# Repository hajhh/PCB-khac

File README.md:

# PCB-khac
CHE1082
CHE1086 2
CHE1092
CHE1058 5
CHE3045
CHE2008 2

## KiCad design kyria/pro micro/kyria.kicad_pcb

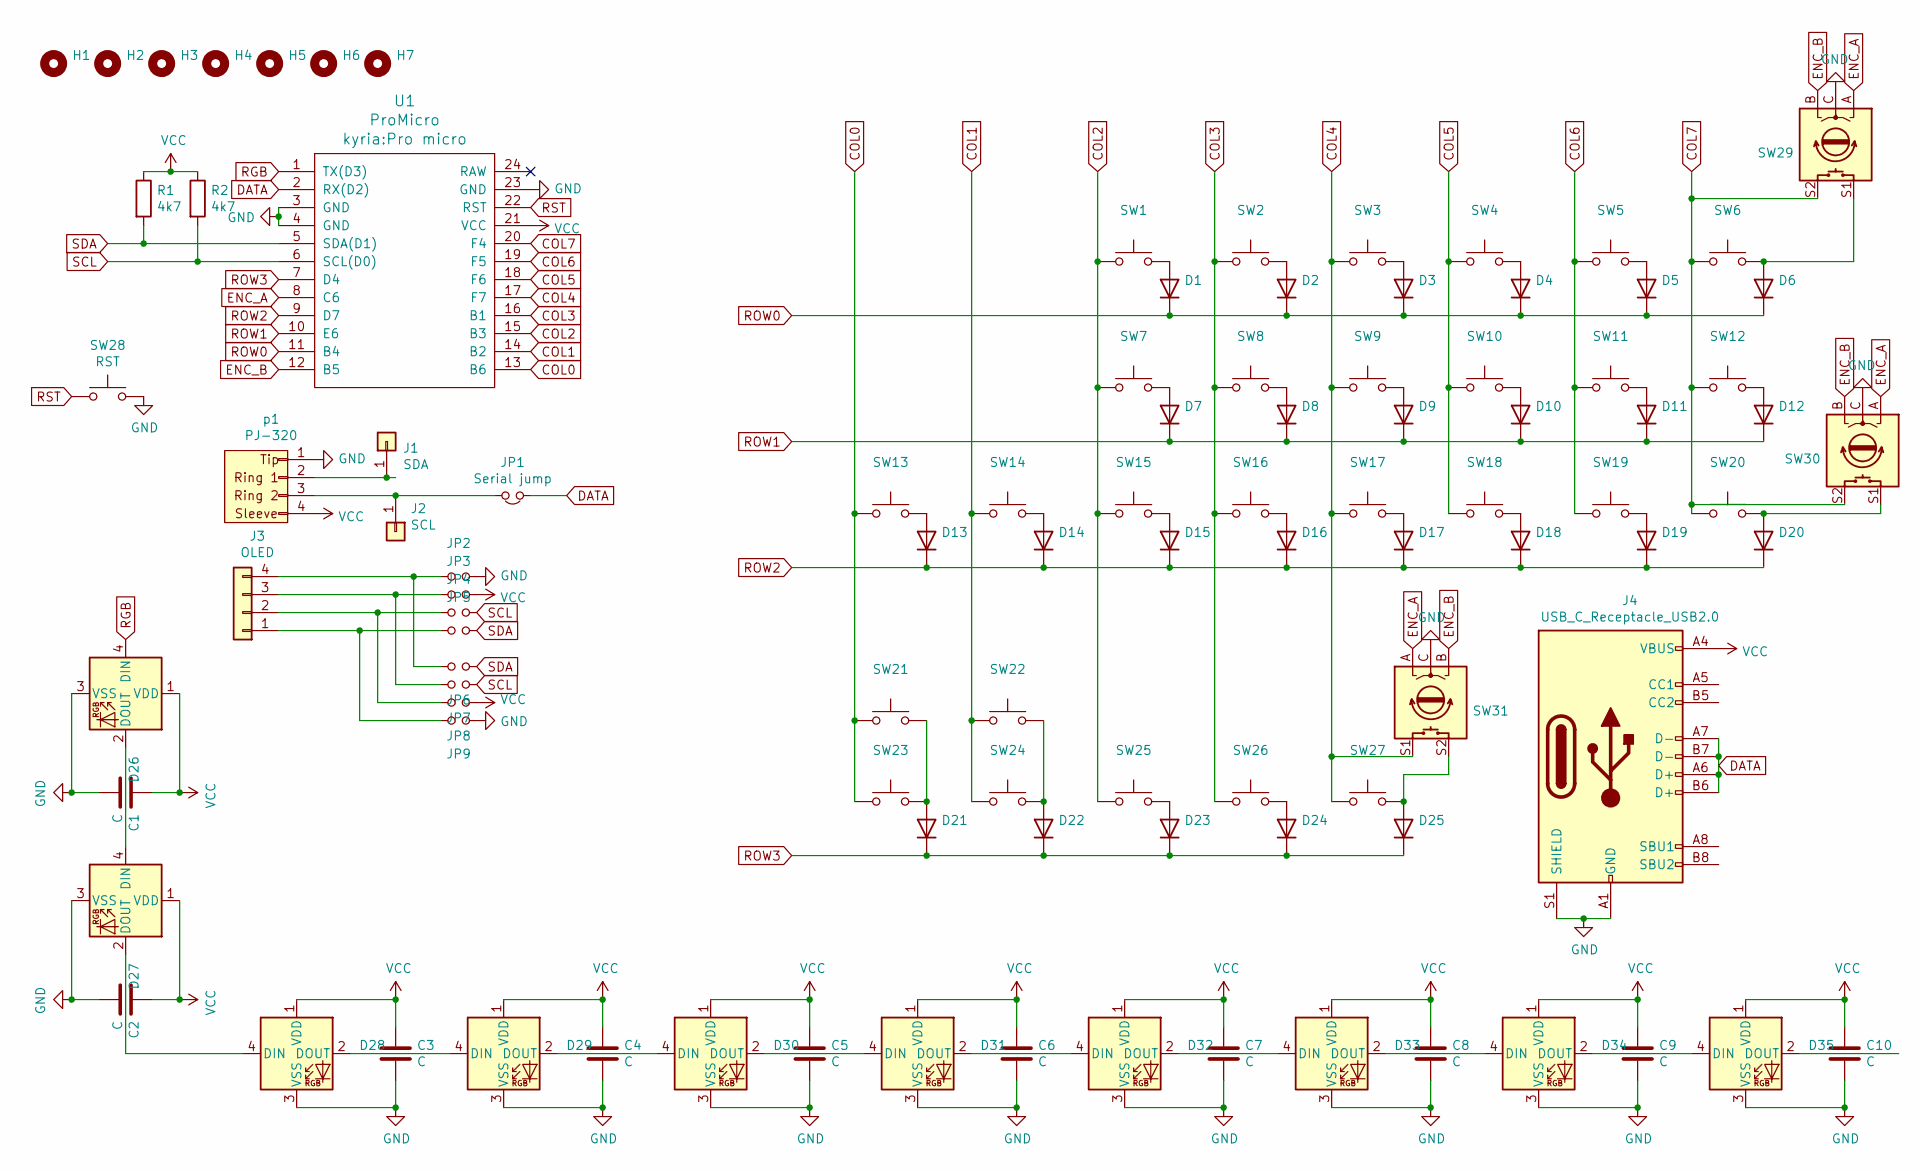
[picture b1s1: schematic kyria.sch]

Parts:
C1, C2, C3, C4, C5, C6, C7, C8, C9, C10: C
D1, D2, D3, D4, D5, D6, D7, D8, D9, D10, D11, D12, D13, D14, D15, D16, D17, D18, D19, D20, D21, D22, D23, D24, D25: Diode_2
D26, D27, D28, D29, D30, D31, D32, D33, D34, D35: WS2812B
H1, H2, H3, H4, H5, H6, H7: Hole
J1: SDA; testpoind
J2: SCL; testpoind
J3: OLED; Conn_01x04
J4: USB_C_Receptacle_USB2.0; TYPE C
JP1: Serial jump; JUMP_NO
JP2, JP3, JP4, JP5, JP6, JP7, JP8, JP9: JUMP_NO
R1, R2: 4k7; R_1
SW1, SW2, SW3, SW4, SW5, SW6, SW7, SW8, SW9, SW10, SW11, SW12, SW13, SW14, SW15, SW16, SW17, SW18, SW19, SW20, SW23, SW24, SW25, SW26, SW27: 1u
SW21, SW22: 2u
SW28: RST; SW_Tactile_SPST_Angled_PTS645Vx31-2LFS
SW29, SW30, SW31: ECODER
U1: ProMicro; Pro micro
p1: PJ-320; PJ-320A

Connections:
COL0: SW13.1, SW21.1, SW23.1, U1.13 (B6)
COL1: SW14.1, SW22.1, SW24.1, U1.14 (B2)
COL2: SW1.1, SW7.1, SW15.1, SW25.1, U1.15 (B3)
COL3: SW2.1, SW8.1, SW16.1, SW26.1, U1.16 (B1)
COL4: SW3.1, SW9.1, SW17.1, SW27.1, SW31.S1, U1.17 (F7)
COL5: SW4.1, SW10.1, SW18.1, U1.18 (F6)
COL6: SW5.1, SW11.1, SW19.1, U1.19 (F5)
COL7: SW6.2, SW12.2, SW20.2, SW29.S2, SW30.S2, U1.20 (F4)
DATA: J4.A6 (D+), J4.A7 (D-), J4.B6 (D+), J4.B7 (D-), JP1.1, U1.2 (RX(D2))
ENC_A: SW29.A, SW30.A, SW31.A, U1.8 (C6)
ENC_B: SW29.B, SW30.B, SW31.B, U1.12 (B5)
GND: C1.2, C2.2, C3.2, C4.2, C5.2, C6.2, C7.2, C8.2, C9.2, C10.2, D26.3 (VSS), D27.3 (VSS), D28.3 (VSS), D29.3 (VSS), D30.3 (VSS), D31.3 (VSS), D32.3 (VSS), D33.3 (VSS), D34.3 (VSS), D35.3 (VSS), J4.A1 (GND), J4.A12 (GND), J4.B1 (GND), J4.B12 (GND), J4.S1 (SHIELD), JP2.2, JP9.2, SW28.2, SW29.C, SW30.C, SW31.C, U1.3 (GND), U1.4 (GND), U1.23 (GND), p1.1
unnamed: D1.2 (A), SW1.2
unnamed: D2.2 (A), SW2.2
unnamed: D3.2 (A), SW3.2
unnamed: D4.2 (A), SW4.2
unnamed: D5.2 (A), SW5.2
unnamed: D6.2 (A), SW6.1, SW29.S1
unnamed: D7.2 (A), SW7.2
unnamed: D8.2 (A), SW8.2
unnamed: D9.2 (A), SW9.2
unnamed: D10.2 (A), SW10.2
unnamed: D11.2 (A), SW11.2
unnamed: D12.2 (A), SW12.1
unnamed: D13.2 (A), SW13.2
unnamed: D14.2 (A), SW14.2
unnamed: D15.2 (A), SW15.2
unnamed: D16.2 (A), SW16.2
unnamed: D17.2 (A), SW17.2
unnamed: D18.2 (A), SW18.2
unnamed: D19.2 (A), SW19.2
unnamed: D20.2 (A), SW20.1, SW30.S1
unnamed: D21.2 (A), SW21.2, SW23.2
unnamed: D22.2 (A), SW22.2, SW24.2
unnamed: D23.2 (A), SW25.2
unnamed: D24.2 (A), SW26.2
unnamed: D25.2 (A), SW27.2, SW31.S2
unnamed: D26.2 (DOUT), D27.4 (DIN)
unnamed: D27.2 (DOUT), D28.4 (DIN)
unnamed: D28.2 (DOUT), D29.4 (DIN)
unnamed: D29.2 (DOUT), D30.4 (DIN)
unnamed: D30.2 (DOUT), D31.4 (DIN)
unnamed: D31.2 (DOUT), D32.4 (DIN)
unnamed: D32.2 (DOUT), D33.4 (DIN)
unnamed: D33.2 (DOUT), D34.4 (DIN)
unnamed: D34.2 (DOUT), D35.4 (DIN)
unnamed: J1.1, p1.2
unnamed: J2.1, JP1.2, p1.3
unnamed: J3.1, JP5.1, JP9.1
unnamed: J3.2, JP4.1, JP8.1
unnamed: J3.3, JP3.1, JP7.1
unnamed: J3.4, JP2.1, JP6.1
RGB: D26.4 (DIN), U1.1 (TX(D3))
ROW0: D1.1 (K), D2.1 (K), D3.1 (K), D4.1 (K), D5.1 (K), D6.1 (K), U1.11 (B4)
ROW1: D7.1 (K), D8.1 (K), D9.1 (K), D10.1 (K), D11.1 (K), D12.1 (K), U1.10 (E6)
ROW2: D13.1 (K), D14.1 (K), D15.1 (K), D16.1 (K), D17.1 (K), D18.1 (K), D19.1 (K), D20.1 (K), U1.9 (D7)
ROW3: D21.1 (K), D22.1 (K), D23.1 (K), D24.1 (K), D25.1 (K), U1.7 (D4)
RST: SW28.1, U1.22 (RST)
SCL: JP4.2, JP7.2, R2.2, U1.6 (SCL(D0))
SDA: JP5.2, JP6.2, R1.2, U1.5 (SDA(D1))
VCC: C1.1, C2.1, C3.1, C4.1, C5.1, C6.1, C7.1, C8.1, C9.1, C10.1, D26.1 (VDD), D27.1 (VDD), D28.1 (VDD), D29.1 (VDD), D30.1 (VDD), D31.1 (VDD), D32.1 (VDD), D33.1 (VDD), D34.1 (VDD), D35.1 (VDD), J4.A4 (VBUS), J4.A9 (VBUS), J4.B4 (VBUS), J4.B9 (VBUS), JP3.2, JP8.2, R1.1, R2.1, U1.21 (VCC), p1.4

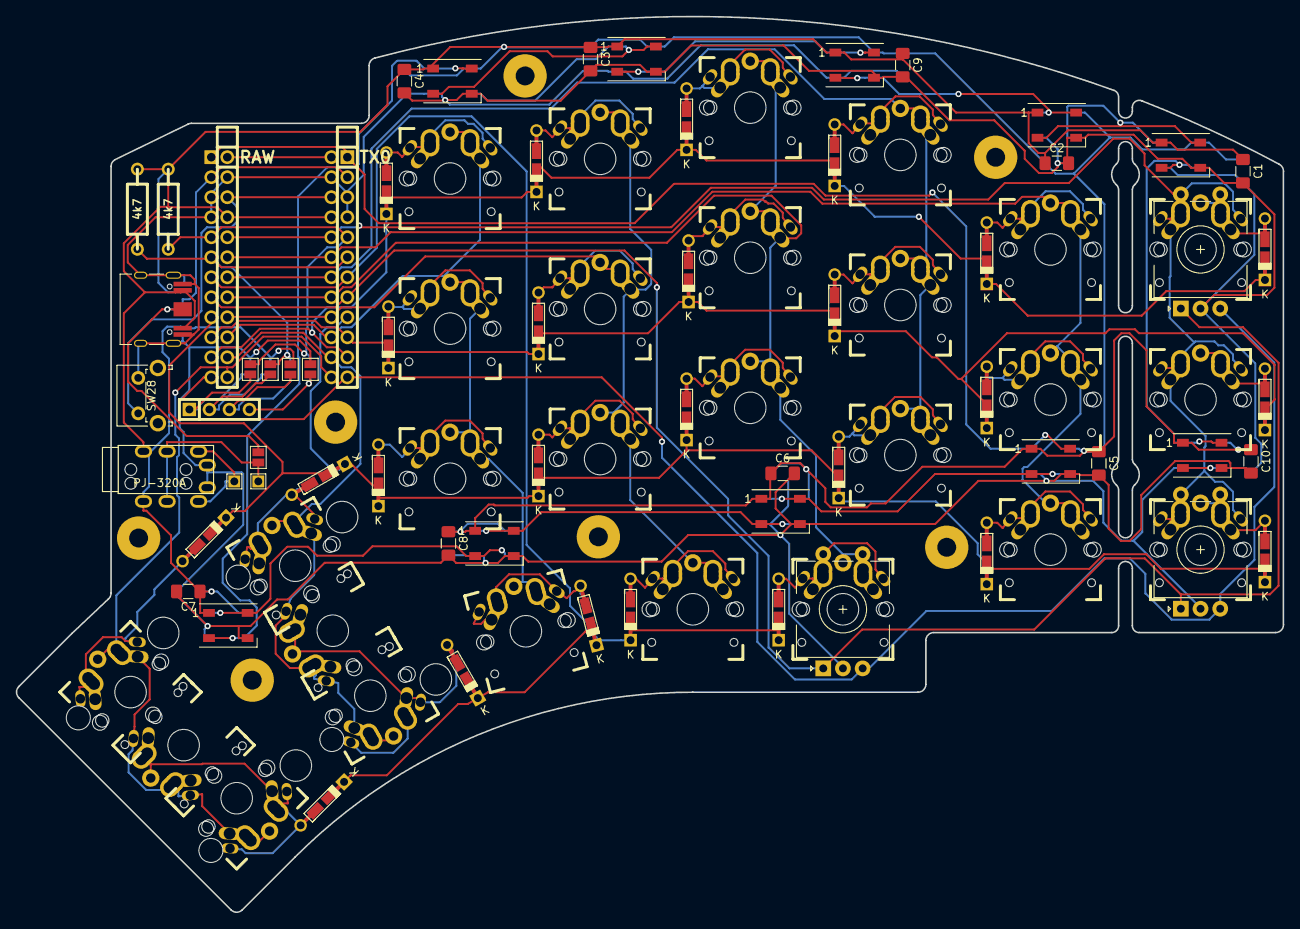
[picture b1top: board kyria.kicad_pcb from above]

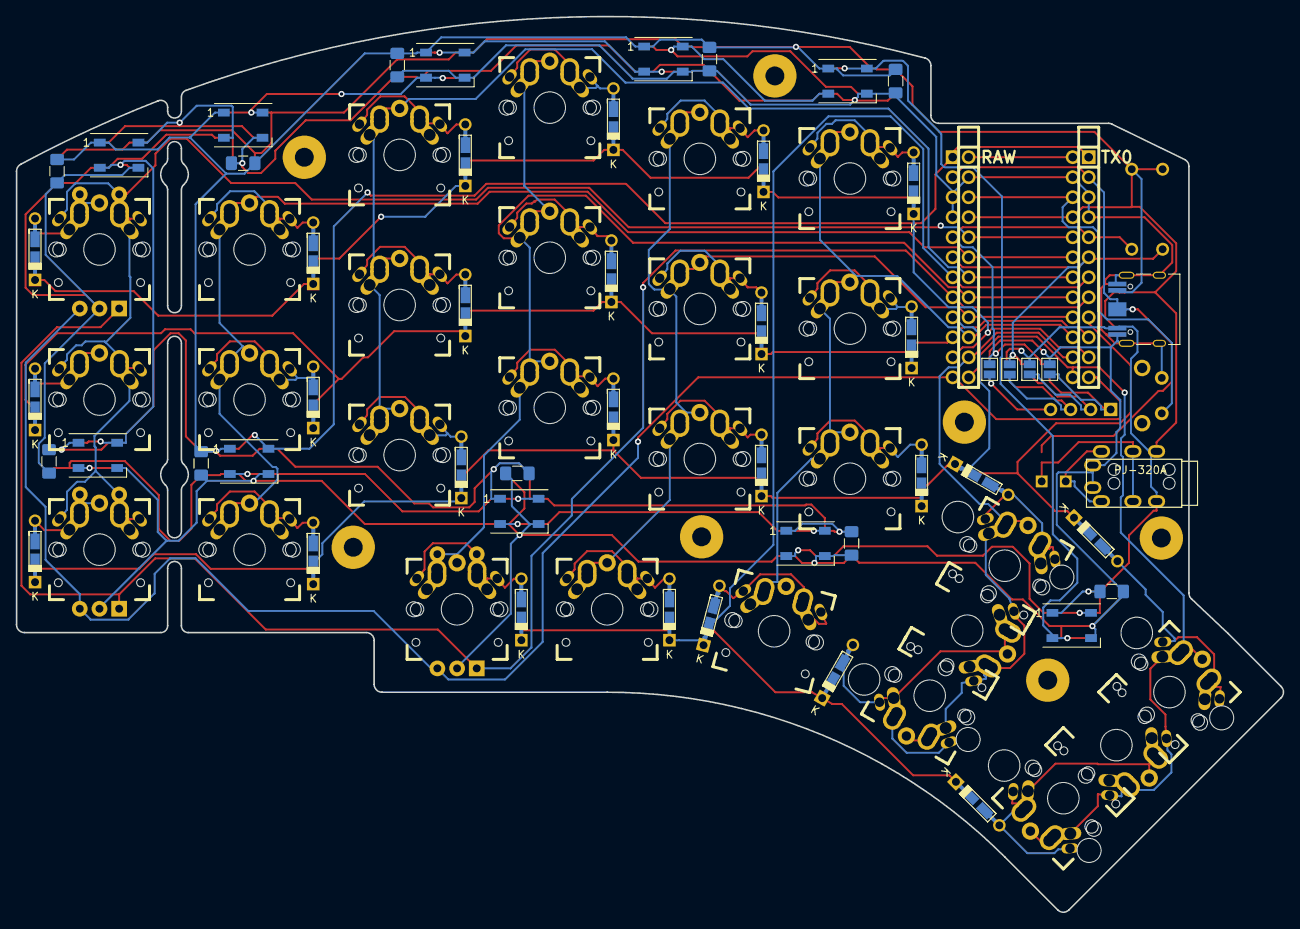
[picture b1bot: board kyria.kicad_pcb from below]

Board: 2 copper layers, 160.8 x 113.7 mm, 100 parts (5 on the bottom side), 61 nets.

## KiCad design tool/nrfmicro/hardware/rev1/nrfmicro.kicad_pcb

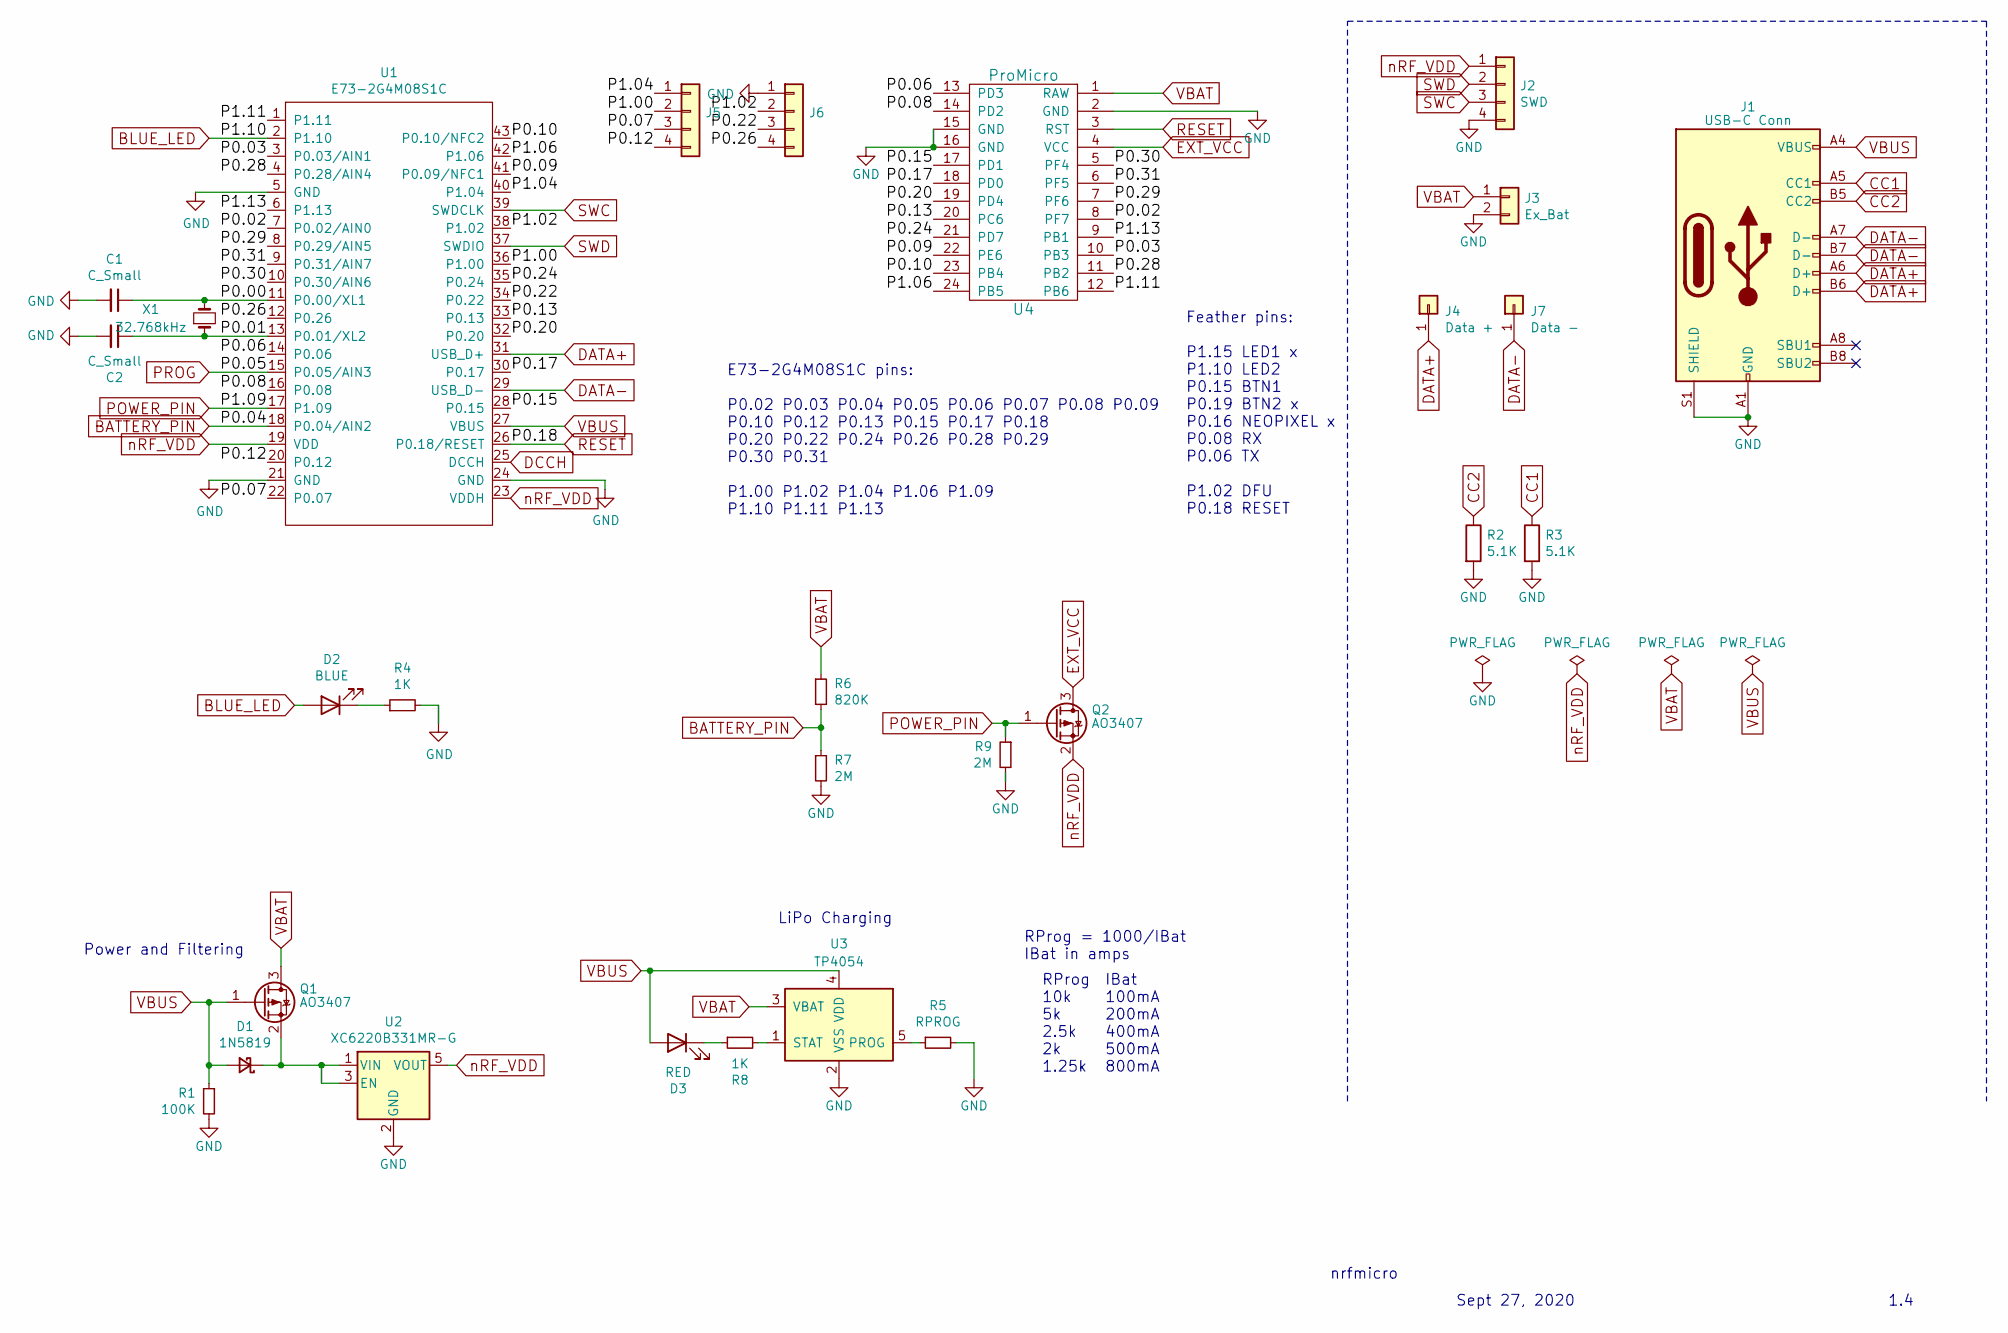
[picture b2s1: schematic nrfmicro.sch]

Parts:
C1, C2: C_Small; C_0603_1608Metric
D1: 1N5819; D_SOD-323F
D2: BLUE; LED_0603_1608Metric
D3: RED; LED_0603_1608Metric
J1: USB-C Conn; usb-c
J2: SWD; connector_swd
J3: Ex_Bat; connector_bat
J4: Data +; PinSocket_1x01_P2.54mm_Vertical
J5, J6: conn_01x04
J7: Data -; PinSocket_1x01_P2.54mm_Vertical
Q1, Q2: AO3407; SOT-23
R1: 100K; R_0603_1608Metric
R2, R3: 5.1K; R_0603_1608Metric
R4, R8: 1K; R_0603_1608Metric
R5: RPROG; R_0603_1608Metric
R6: 820K; R_0603_1608Metric
R7, R9: 2M; R_0603_1608Metric
U1: E73-2G4M08S1C; E73-2G4M08S1C-52840
U2: XC6220B331MR-G; SOT-23-5
U3: TP4054; SOT-23-5
U4: ProMicro; pro_micro
X1: 32.768kHz; Crystal_SMD_MicroCrystal_CM9V-T1A-2Pin_1.6x1.0mm

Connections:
/P0.00: C1.1, U1.11 (P0.00/XL1), X1.2
/P0.01: C2.1, U1.13 (P0.01/XL2), X1.1
/P0.02: U1.7 (P0.02/AIN0), U4.8 (PF7)
/P0.03: U1.3 (P0.03/AIN1), U4.10 (PB3)
/P0.06: U1.14 (P0.06), U4.13 (PD3)
/P0.07: J5.3, U1.22 (P0.07)
/P0.08: U1.16 (P0.08), U4.14 (PD2)
/P0.09: U1.41 (P0.09/NFC1), U4.22 (PE6)
/P0.10: U1.43 (P0.10/NFC2), U4.23 (PB4)
/P0.12: J5.4, U1.20 (P0.12)
/P0.13: U1.33 (P0.13), U4.20 (PC6)
/P0.15: U1.28 (P0.15), U4.17 (PD1)
/P0.17: U1.30 (P0.17), U4.18 (PD0)
/P0.20: U1.32 (P0.20), U4.19 (PD4)
/P0.22: J6.3, U1.34 (P0.22)
/P0.24: U1.35 (P0.24), U4.21 (PD7)
/P0.26: J6.4, U1.12 (P0.26)
/P0.28: U1.4 (P0.28/AIN4), U4.11 (PB2)
/P0.29: U1.8 (P0.29/AIN5), U4.7 (PF6)
/P0.30: U1.10 (P0.30/AIN6), U4.5 (PF4)
/P0.31: U1.9 (P0.31/AIN7), U4.6 (PF5)
/P1.00: J5.2, U1.36 (P1.00)
/P1.02: J6.2, U1.38 (P1.02)
/P1.04: J5.1, U1.40 (P1.04)
/P1.06: U1.42 (P1.06), U4.24 (PB5)
/P1.11: U1.1 (P1.11), U4.12 (PB6)
/P1.13: U1.6 (P1.13), U4.9 (PB1)
BATTERY_PIN: R6.2, R7.1, U1.18 (P0.04/AIN2)
BLUE_LED: D2.2 (A), U1.2 (P1.10)
CC1: J1.A5 (CC1), R3.1
CC2: J1.B5 (CC2), R2.1
DATA+: J1.A6 (D+), J1.B6 (D+), J4.1, U1.31 (USB_D+)
DATA-: J1.A7 (D-), J1.B7 (D-), J7.1, U1.29 (USB_D-)
DCCH: U1.25 (DCCH)
EXT_VCC: Q2.3 (D), U4.4 (VCC)
GND: C1.2, C2.2, J1.A1 (GND), J1.A12 (GND), J1.B1 (GND), J1.B12 (GND), J1.S1 (SHIELD), J2.4, J3.2, J6.1, R1.2, R2.2, R3.2, R4.2, R5.2, R7.2, R9.2, U1.5 (GND), U1.21 (GND), U1.24 (GND), U2.2 (GND), U3.2 (VSS), U4.2 (GND), U4.15 (GND), U4.16 (GND)
unnamed: D1.1 (K), Q1.2 (S), U2.1 (VIN), U2.3 (EN)
unnamed: D2.1 (K), R4.1
unnamed: D3.1 (K), R8.1
unnamed: R5.1, U3.5 (PROG)
unnamed: R8.2, U3.1 (STAT)
POWER_PIN: Q2.1 (G), R9.1, U1.17 (P1.09)
PROG: U1.15 (P0.05/AIN3)
RESET: U1.26 (P0.18/RESET), U4.3 (RST)
SWC: J2.3, U1.39 (SWDCLK)
SWD: J2.2, U1.37 (SWDIO)
VBAT: J3.1, Q1.3 (D), R6.1, U3.3 (VBAT), U4.1 (RAW)
VBUS: D1.2 (A), D3.2 (A), J1.A4 (VBUS), J1.A9 (VBUS), J1.B4 (VBUS), J1.B9 (VBUS), Q1.1 (G), R1.1, U1.27 (VBUS), U3.4 (VDD)
nRF_VDD: J2.1, Q2.2 (S), U1.19 (VDD), U1.23 (VDDH), U2.5 (VOUT)

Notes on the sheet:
nrfmicro
Sept 27, 2020
1.4
E73-2G4M08S1C pins: P0.02 P0.03 P0.04 P0.05 P0.06 P0.07 P0.08 P0.09 P0.10 P0.12 P0.13 P0.15 P0.17 P0.18 P0.20 P0.22 P0.24 P0.26 P0.28 P0.29 P0.30 P0.31 P1.00 P1.02 P1.04 P1.06 P1.09 P1.10 P1.11 P1.13
Feather pins: P1.15 LED1 x P1.10 LED2 P0.15 BTN1 P0.19 BTN2 x P0.16 NEOPIXEL x P0.08 RX P0.06 TX P1.02 DFU P0.18 RESET
Power and Filtering
LiPo Charging
RProg 10k 5k 2.5k 2k 1.25k
IBat 100mA 200mA 400mA 500mA 800mA
RProg = 1000/IBat IBat in amps

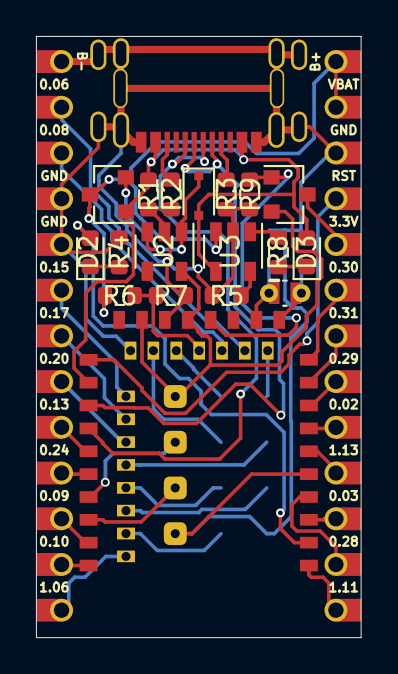
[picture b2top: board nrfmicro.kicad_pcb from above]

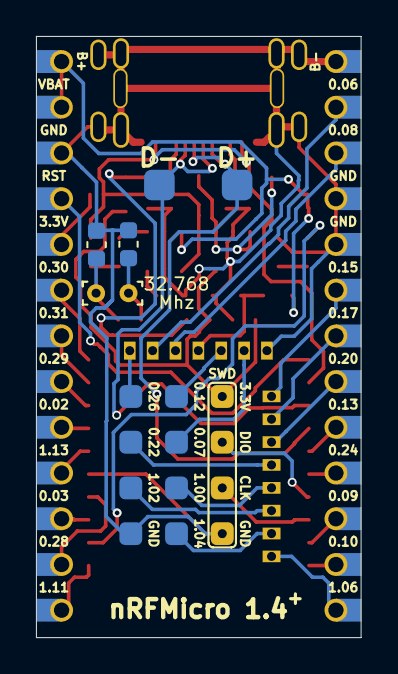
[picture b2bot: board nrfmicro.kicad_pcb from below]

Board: 2 copper layers, 18.0 x 33.4 mm, 28 parts (7 on the bottom side), 47 nets.

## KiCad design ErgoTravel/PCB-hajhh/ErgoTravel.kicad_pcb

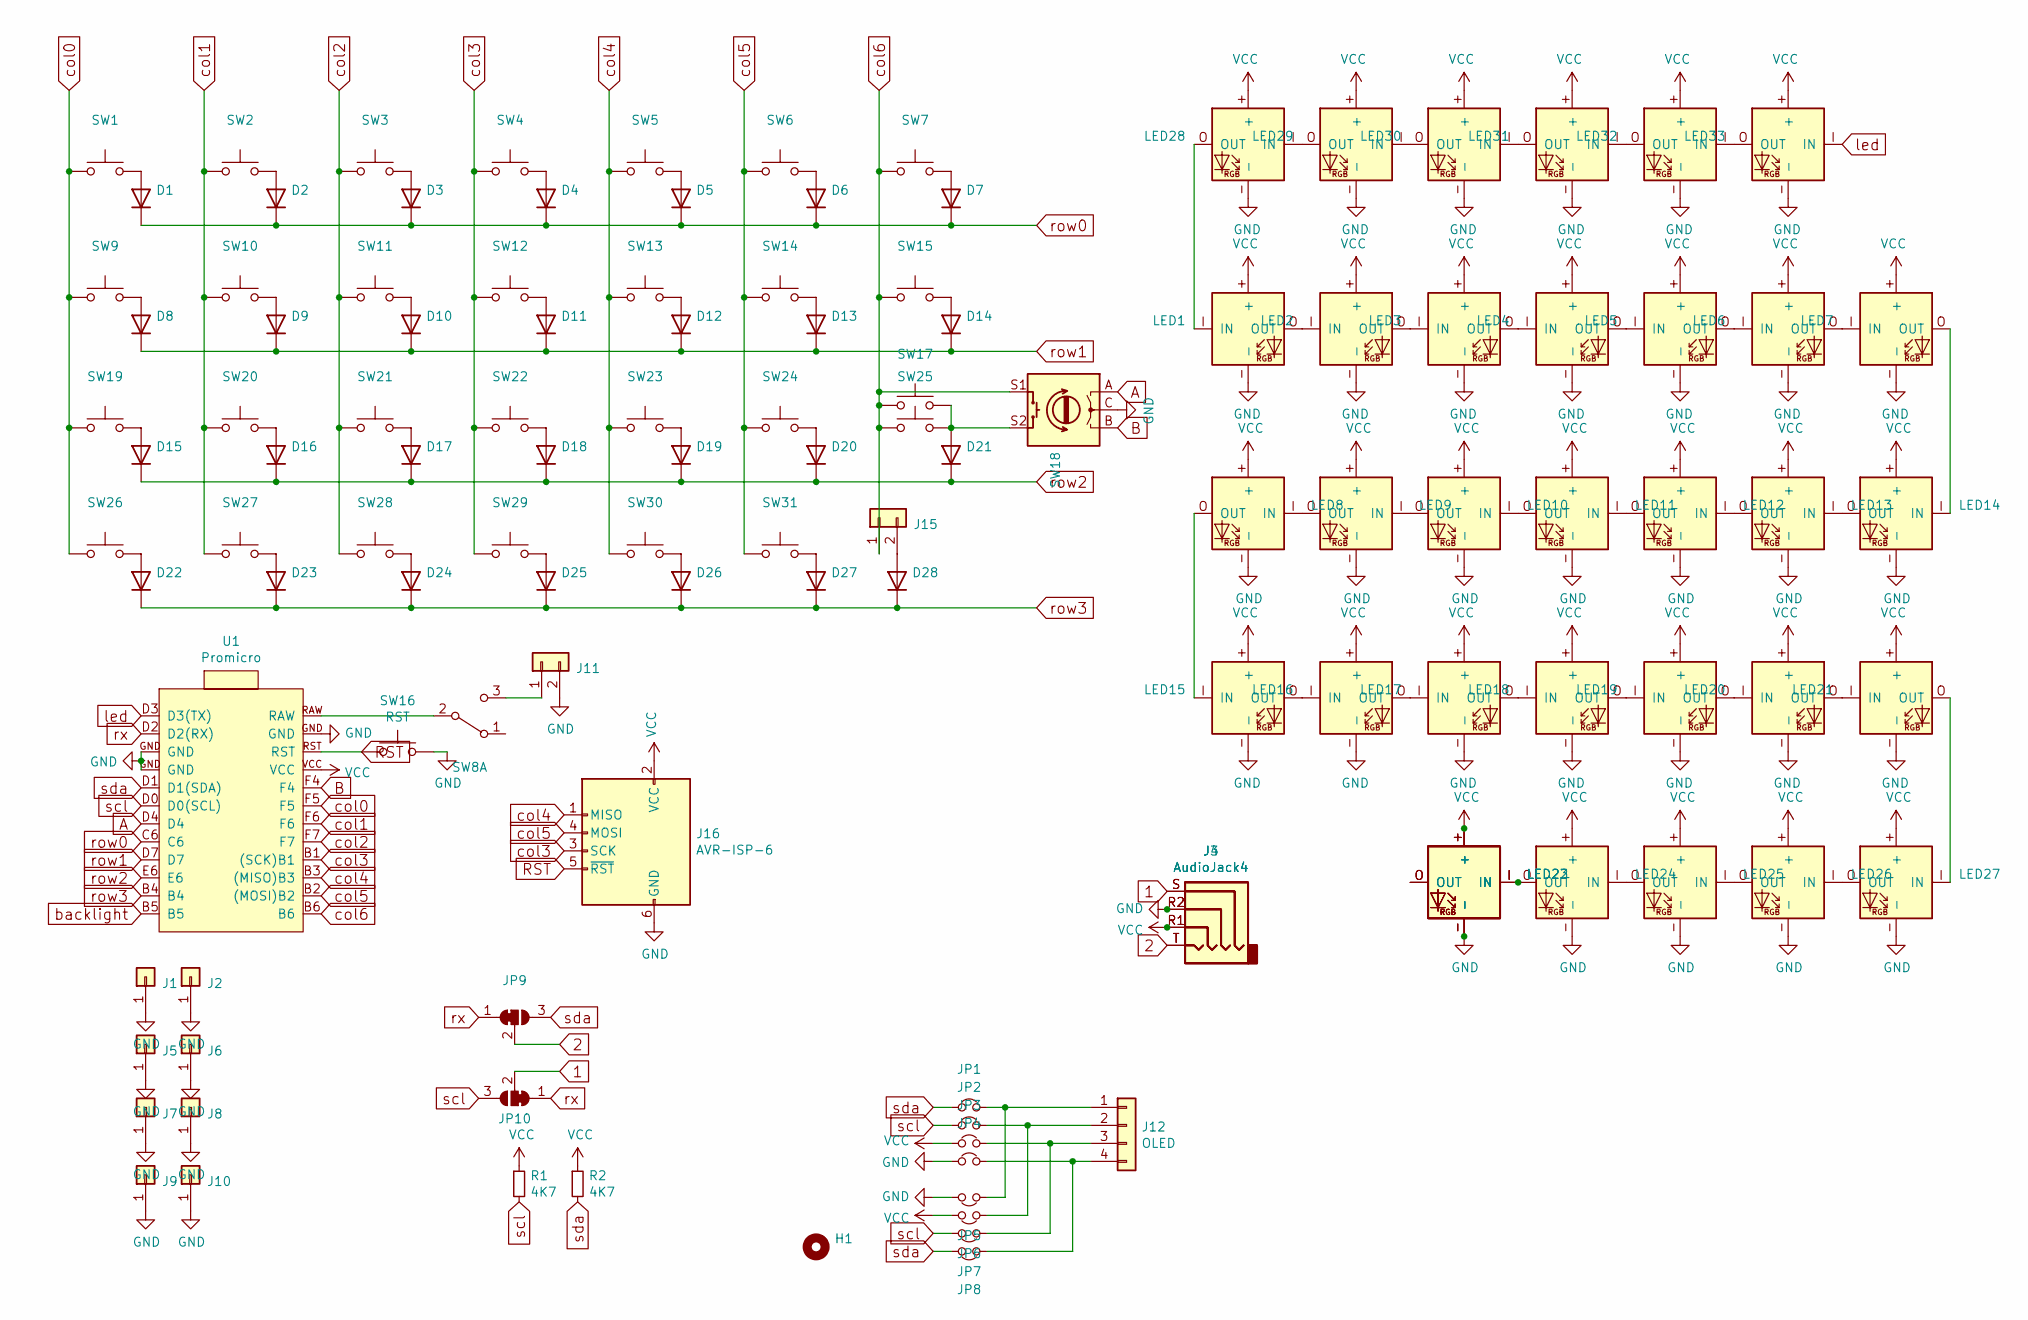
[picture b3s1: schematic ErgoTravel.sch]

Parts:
D1, D2, D3, D4, D5, D6, D7, D8, D9, D10, D11, D12, D13, D14, D15, D16, D17, D18, D19, D20, D21, D22, D23, D24, D25, D26, D27, D28: DIODE
H1: Stab
J1, J2, J5, J6, J7, J8, J9, J10: MountingHole_2.2mm_M2_DIN965_Pad
J3, J4: AudioJack4; Jack_3.5mm_PJ320D_Horizontal
J11, J15: PinHeader_1x02_P2.54mm_Vertical
J12: OLED; OLED-0.91
J16: AVR-ISP-6; PinHeader_2x03_P2.54mm_Vertical
JP1, JP2, JP3, JP4, JP5, JP6, JP7, JP8: Jump
JP9, JP10: SolderJumper-3_P1.3mm_Bridged12_Pad1.0x1.5mm_NumberLabels
LED1, LED2, LED3, LED4, LED5, LED6, LED7, LED15, LED16, LED17, LED18, LED19, LED20, LED23: SK6812mini-e-R2L
LED8, LED9, LED10, LED11, LED12, LED13, LED14, LED21, LED22, LED24, LED25, LED26, LED27: SK6812mini-e-L2R
LED28, LED29, LED30, LED31, LED32, LED33: SK6812MINI-FLIP
R1, R2: 4K7; R_0805_2012Metric
SW1, SW2, SW3, SW4, SW5, SW6, SW7, SW9, SW10, SW11, SW12, SW13, SW14, SW15, SW17, SW19, SW20, SW21, SW22, SW23, SW24, SW25, SW26, SW27, SW28, SW29, SW30, SW31: SW-1u-Aps-Split
SW8: SW_SPDT_PCM12
SW16: RST; SW_TACT_ALPS_SKQGABE010
SW18: Econder
U1: Promicro; PRO-MICRO

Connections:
1: J3.S, J4.S, JP10.2 (C)
2: J3.T, J4.T, JP9.2 (C)
A: SW18.A, U1.D4
B: SW18.B, U1.F4
GND: J1.1, J2.1, J3.R2, J4.R2, J5.1, J6.1, J7.1, J8.1, J9.1, J10.1, J11.2, J16.6 (GND), JP4.1, JP5.1, LED1.-, LED2.-, LED3.-, LED4.-, LED5.-, LED6.-, LED7.-, LED8.-, LED9.-, LED10.-, LED11.-, LED12.-, LED13.-, LED14.-, LED15.-, LED16.-, LED17.-, LED18.-, LED19.-, LED20.-, LED21.-, LED22.-, LED23.-, LED24.-, LED25.-, LED26.-, LED27.-, LED28.-, LED29.-, LED30.-, LED31.-, LED32.-, LED33.-, SW16.2, SW18.C, U1.GND
unnamed: D1.2 (A), SW1.2
unnamed: D2.2 (A), SW2.2
unnamed: D3.2 (A), SW3.2
unnamed: D4.2 (A), SW4.1
unnamed: D5.2 (A), SW5.2
unnamed: D6.2 (A), SW6.2
unnamed: D7.2 (A), SW7.2
unnamed: D8.2 (A), SW9.2
unnamed: D9.2 (A), SW10.2
unnamed: D10.2 (A), SW11.2
unnamed: D11.2 (A), SW12.2
unnamed: D12.2 (A), SW13.2
unnamed: D13.2 (A), SW14.2
unnamed: D14.2 (A), SW15.2
unnamed: D15.2 (A), SW19.2
unnamed: D16.2 (A), SW20.2
unnamed: D17.2 (A), SW21.2
unnamed: D18.2 (A), SW22.2
unnamed: D19.2 (A), SW23.2
unnamed: D20.2 (A), SW24.2
unnamed: D21.2 (A), SW17.2, SW18.S2, SW25.1
unnamed: D22.2 (A), SW26.2
unnamed: D23.2 (A), SW27.2
unnamed: D24.2 (A), SW28.2
unnamed: D25.2 (A), SW29.2
unnamed: D26.2 (A), SW30.2
unnamed: D27.2 (A), SW31.2
unnamed: D28.2 (A), J15.2
unnamed: J11.1, SW8.3 (C)
unnamed: J12.1, JP1.2, JP5.2
unnamed: J12.2, JP2.2, JP6.2
unnamed: J12.3, JP3.2, JP7.2
unnamed: J12.4, JP4.2, JP8.2
unnamed: LED1.I (IN), LED28.O (OUT)
unnamed: LED1.O (OUT), LED2.I (IN)
unnamed: LED2.O (OUT), LED3.I (IN)
unnamed: LED3.O (OUT), LED4.I (IN)
unnamed: LED4.O (OUT), LED5.I (IN)
unnamed: LED5.O (OUT), LED6.I (IN)
unnamed: LED6.O (OUT), LED7.I (IN)
unnamed: LED8.I (IN), LED9.O (OUT)
unnamed: LED10.I (IN), LED11.O (OUT)
unnamed: LED9.I (IN), LED10.O (OUT)
unnamed: LED11.I (IN), LED12.O (OUT)
unnamed: LED12.I (IN), LED13.O (OUT)
unnamed: LED13.I (IN), LED14.O (OUT)
unnamed: LED7.O (OUT), LED14.I (IN)
unnamed: LED8.O (OUT), LED15.I (IN)
unnamed: LED15.O (OUT), LED16.I (IN)
unnamed: LED16.O (OUT), LED17.I (IN)
unnamed: LED17.O (OUT), LED18.I (IN)
unnamed: LED18.O (OUT), LED19.I (IN)
unnamed: LED19.O (OUT), LED20.I (IN)
unnamed: LED20.O (OUT), LED21.I (IN)
unnamed: LED21.O (OUT), LED27.I (IN)
unnamed: LED22.I (IN), LED23.I (IN), LED24.O (OUT)
unnamed: LED22.O (OUT), LED23.O (OUT)
unnamed: LED24.I (IN), LED25.O (OUT)
unnamed: LED25.I (IN), LED26.O (OUT)
unnamed: LED26.I (IN), LED27.O (OUT)
unnamed: LED28.I (IN), LED29.O (OUT)
unnamed: LED29.I (IN), LED30.O (OUT)
unnamed: LED30.I (IN), LED31.O (OUT)
unnamed: LED31.I (IN), LED32.O (OUT)
unnamed: LED32.I (IN), LED33.O (OUT)
unnamed: SW8.2 (B), U1.RAW
RST: J16.5 (~RST), SW16.1, U1.RST
VCC: J3.R1, J4.R1, J16.2 (VCC), JP3.1, JP6.1, LED1.+, LED2.+, LED3.+, LED4.+, LED5.+, LED6.+, LED7.+, LED8.+, LED9.+, LED10.+, LED11.+, LED12.+, LED13.+, LED14.+, LED15.+, LED16.+, LED17.+, LED18.+, LED19.+, LED20.+, LED21.+, LED22.+, LED23.+, LED24.+, LED25.+, LED26.+, LED27.+, LED28.+, LED29.+, LED30.+, LED31.+, LED32.+, LED33.+, R1.1, R2.1, U1.VCC
backlight: U1.B5
col0: SW1.1, SW9.1, SW19.1, SW26.1, U1.F5
col1: SW2.1, SW10.1, SW20.1, SW27.1, U1.F6
col2: SW3.1, SW11.1, SW21.1, SW28.1, U1.F7
col3: J16.3 (SCK), SW4.2, SW12.1, SW22.1, SW29.1, U1.B1 ((SCK)B1)
col4: J16.1 (MISO), SW5.1, SW13.1, SW23.1, SW30.1, U1.B3 ((MISO)B3)
col5: J16.4 (MOSI), SW6.1, SW14.1, SW24.1, SW31.1, U1.B2 ((MOSI)B2)
col6: J15.1, SW7.1, SW15.1, SW17.1, SW18.S1, SW25.2, U1.B6
led: LED33.I (IN), U1.D3 (D3(TX))
row0: D1.1 (K), D2.1 (K), D3.1 (K), D4.1 (K), D5.1 (K), D6.1 (K), D7.1 (K), U1.C6
row1: D8.1 (K), D9.1 (K), D10.1 (K), D11.1 (K), D12.1 (K), D13.1 (K), D14.1 (K), U1.D7
row2: D15.1 (K), D16.1 (K), D17.1 (K), D18.1 (K), D19.1 (K), D20.1 (K), D21.1 (K), U1.E6
row3: D22.1 (K), D23.1 (K), D24.1 (K), D25.1 (K), D26.1 (K), D27.1 (K), D28.1 (K), U1.B4
rx: JP9.1 (A), JP10.1 (A), U1.D2 (D2(RX))
scl: JP2.1, JP7.1, JP10.3 (B), R1.2, U1.D0 (D0(SCL))
sda: JP1.1, JP8.1, JP9.3 (B), R2.2, U1.D1 (D1(SDA))

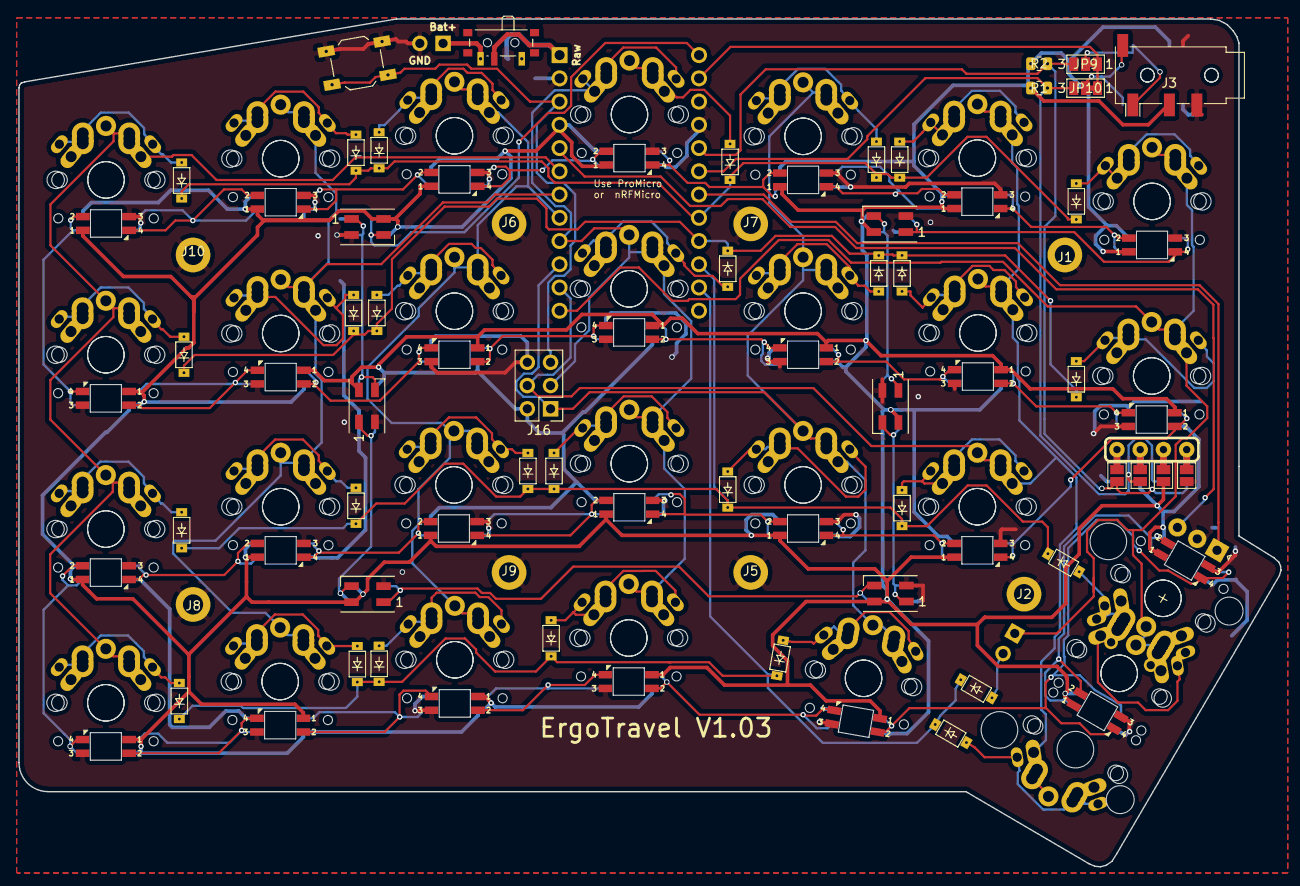
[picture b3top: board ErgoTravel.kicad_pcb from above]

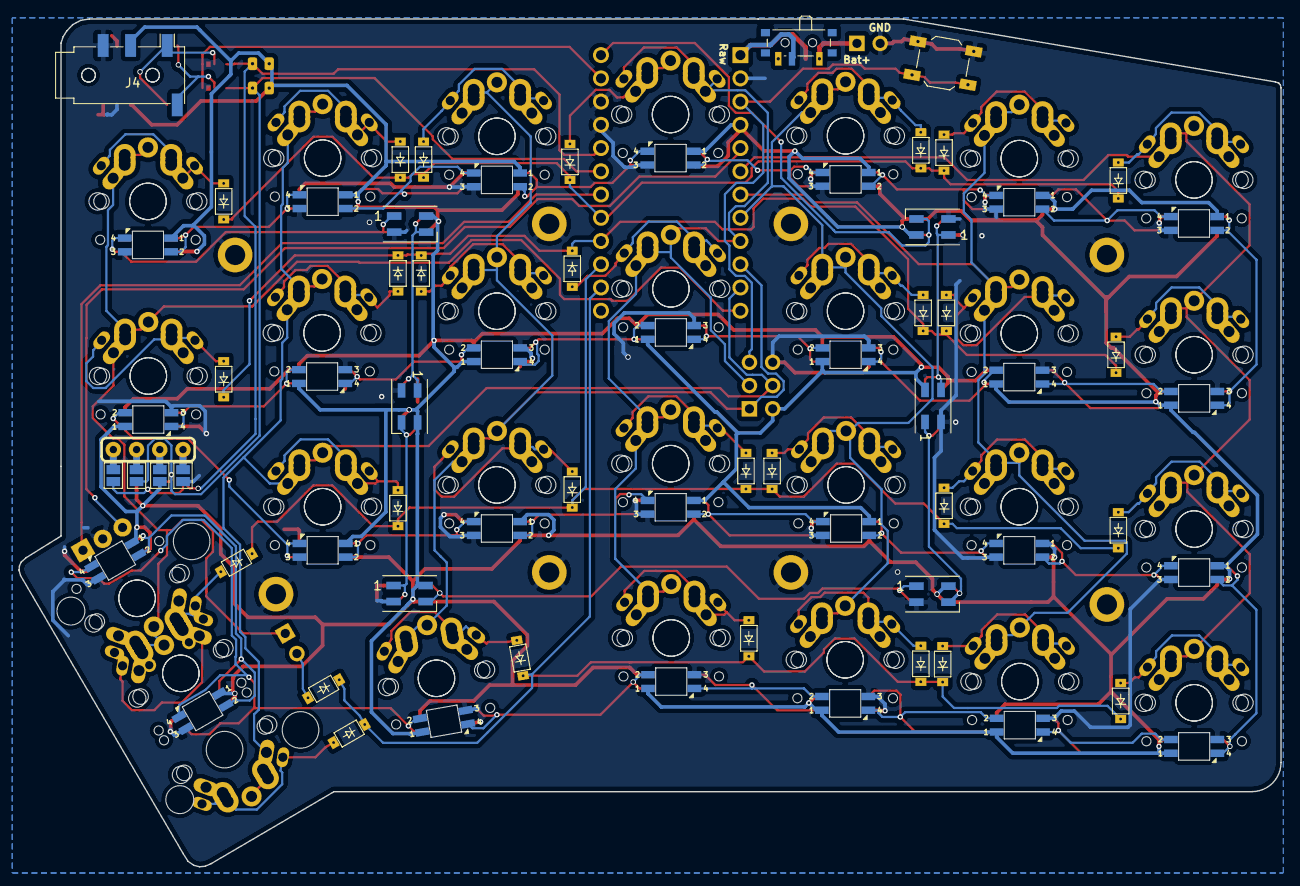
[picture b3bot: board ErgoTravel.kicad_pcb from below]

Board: 2 copper layers, 137.9 x 92.7 mm, 120 parts (7 on the bottom side), 88 nets.
